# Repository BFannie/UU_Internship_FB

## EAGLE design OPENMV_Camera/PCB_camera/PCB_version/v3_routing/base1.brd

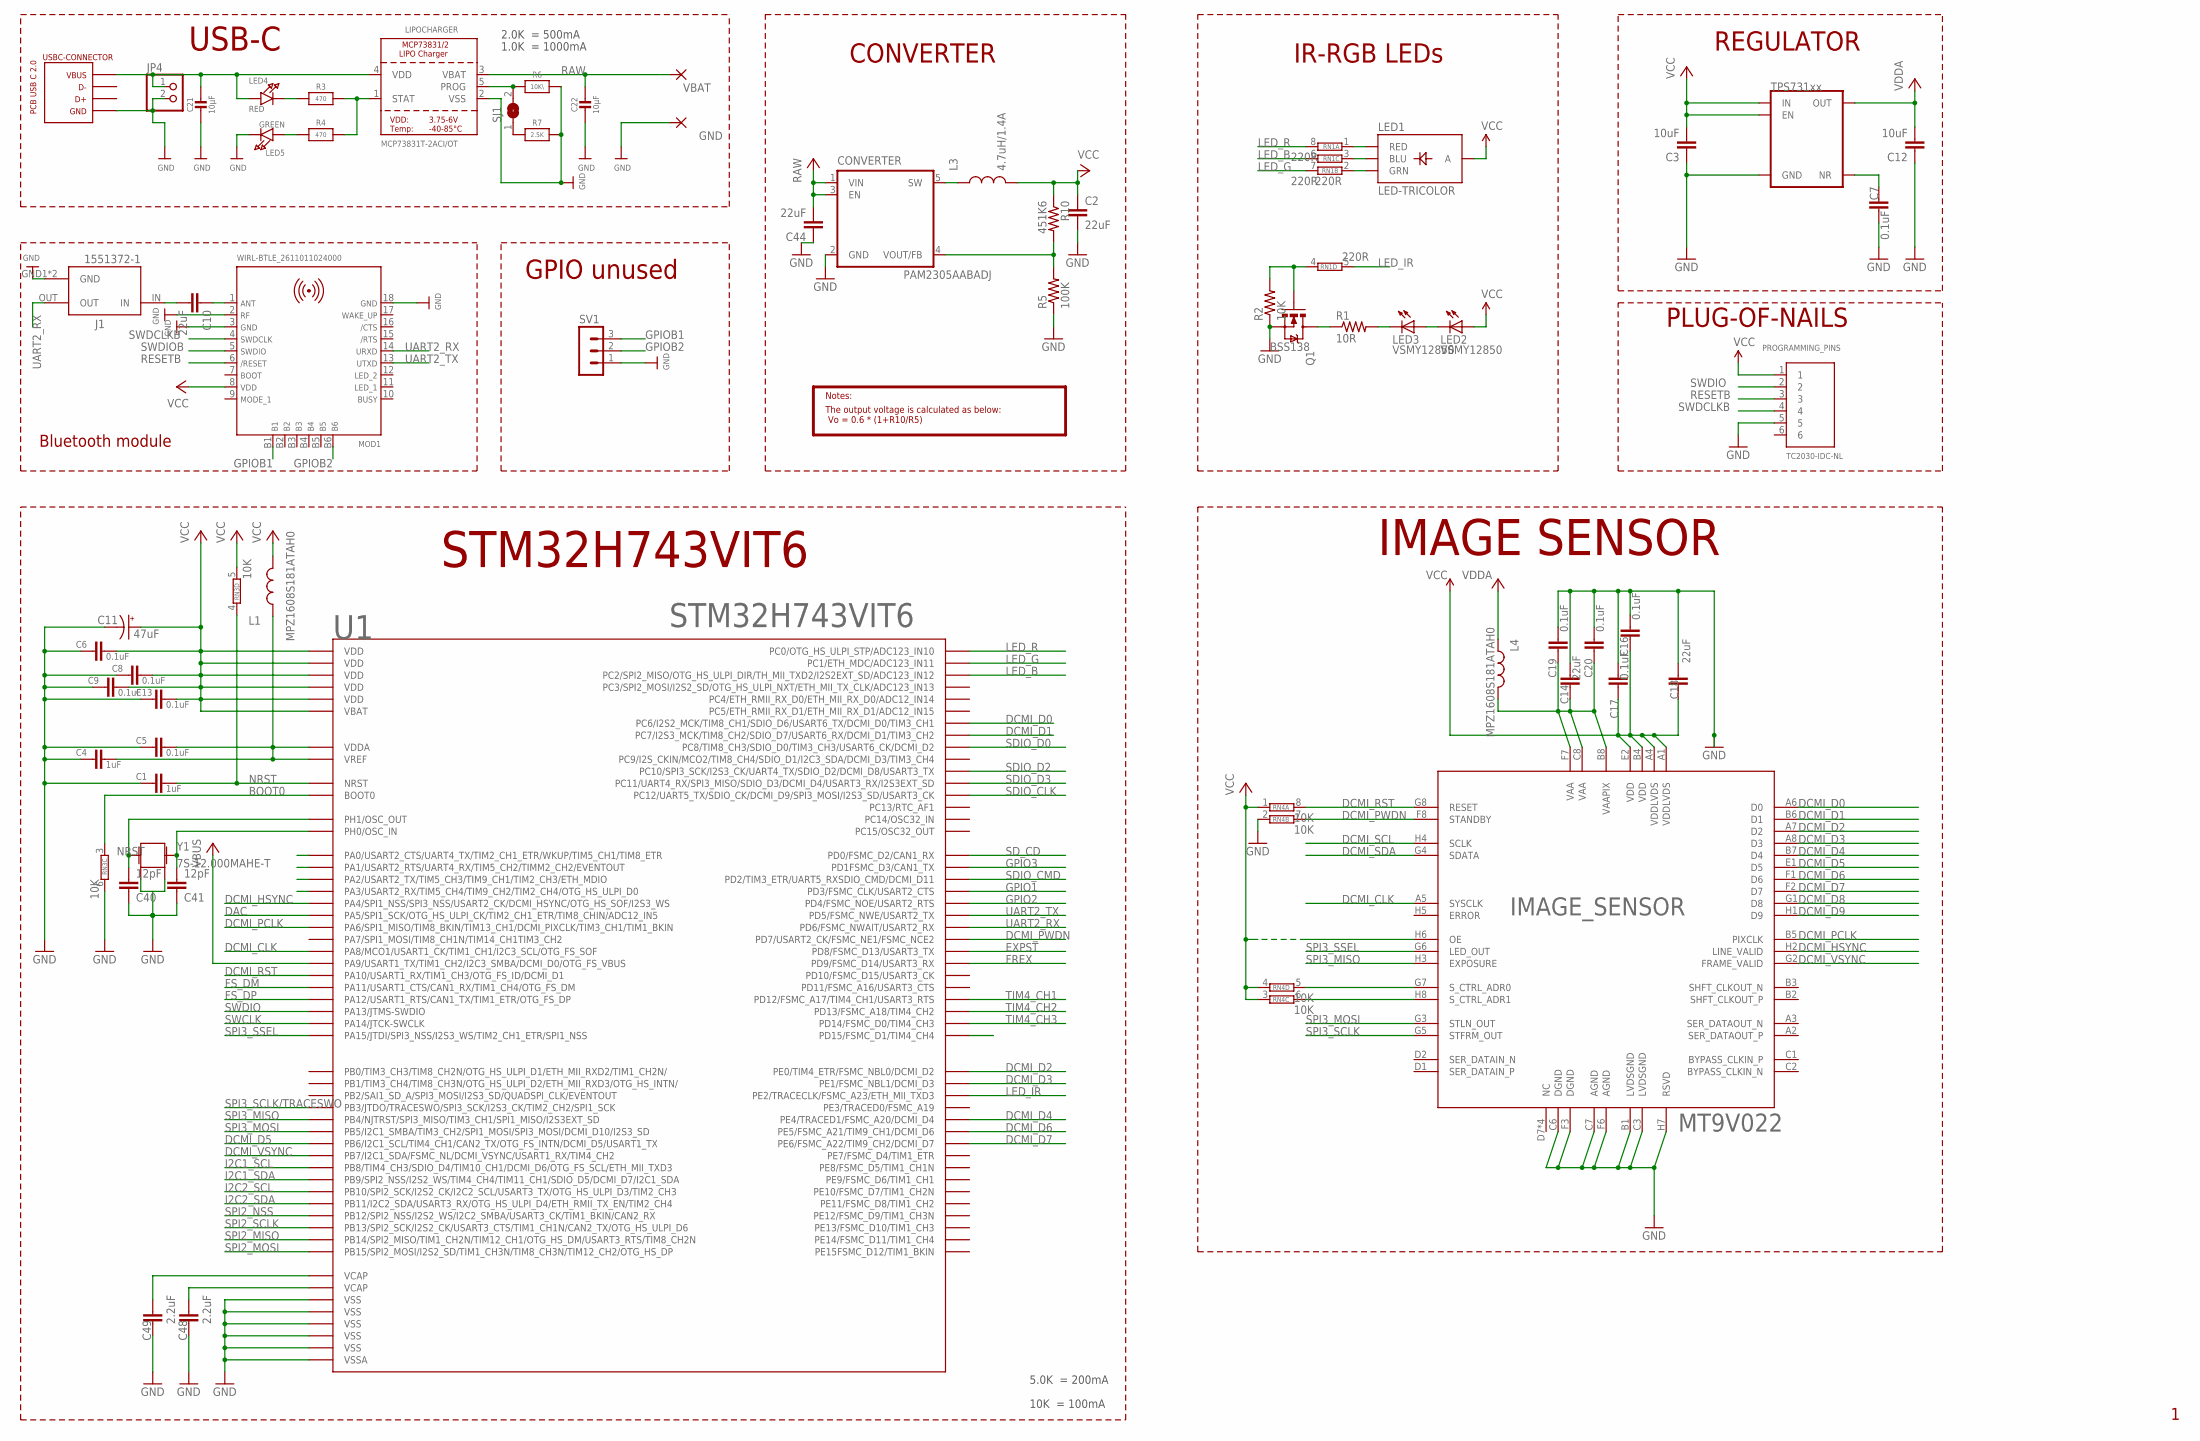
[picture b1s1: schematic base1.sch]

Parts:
C1, C4: 1uF; 0603-CAP
C2, C10, C14, C18, C44: 22uF; 0805
C3, C12: 10uF; 0805
C5, C6, C7, C8, C9, C13: 0.1uF; 0603-CAP
C11: 47uF; EIA3216
C16, C17, C19, C20: 0.1uF; 0402-CAP
C21, C22: 10µF; 0805-NO
C40, C41: 12pF; 0603-CAP
C48, C49: 2.2uF; 0603-CAP
CONVERTER: PAM2305AABADJ; TSOT25
GND: SMD2; SMD1,27-2,54
IMAGE_SENSOR: MT9V022; IBGA52
J1: 1551372-1; TE_1551372-1
JP4: HEADER-1X2ROUND; 1X02_ROUND
L1, L4: MPZ1608S181ATAH0; 0603
L3: 4.7uH/1.4A; 1007
LED1: LED-TRICOLOR; LED-TRICOLOR-SMD-MF
LED2, LED3: VSMY12850; LED-1206
LED4: RED; CHIPLED_0805_NOOUTLINE
LED5: GREEN; CHIPLED_0805_NOOUTLINE
LIPOCHARGER: MCP73831T-2ACI/OT; SOT23-5
MOD1: WIRL-BTLE_2611011024000; WE-FP-4+
PROGRAMMING_PINS: TC2030-IDC-NL; TAG_TC2030-IDC-NL
Q1: BSS138; SOT23-3
R1: 10R; 0603-RES
R2: 10K; 0603-RES
R3, R4: 470; 0805-NO
R5: 100K; 0603-RES
R6: 10K\; 0805-NO
R7: 2.5K; 0805-NO
R10: 451K6; 0603-RES
REGULATOR: TPS731XX; SOT23-5
RN1: 220R; EXBV8V
RN3, RN4: 10K; EXBV8V
SJ1: SOLDERJUMPER; SOLDERJUMPER_ARROW_NOPASTE
SV1: MA03-1
U1: STM32H743VIT6; LQFP100
USBC-CONNECTOR: PCB_USB_C_2.0DS_2; USB_TYPE_C_DS_2
VBAT: SMD2; SMD1,27-2,54
Y1: 7S-12.000MAHE-T; CRYSTAL-2.5X2.0

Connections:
BOOT0: RN3.3 (1), U1.94 (BOOT0)
DAC: U1.29 (PA5/SPI1_SCK/OTG_HS_ULPI_CK/TIM2_CH1_ET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)
DCMI_CLK: IMAGE_SENSOR.A5 (SYSCLK), U1.67 (PA8/MCO1/USART1_CK/TIM1_CH1/I2C3_SCL/OT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)
DCMI_D0: IMAGE_SENSOR.A6 (D0), U1.63 (PC6/I2S2_MCK/TIM8_CH1/SDIO_D6/USART6_TX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)
DCMI_D1: IMAGE_SENSOR.B6 (D1), U1.64 (PC7/I2S3_MCK/TIM8_CH2/SDIO_D7/USART6_RX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)
DCMI_D2: IMAGE_SENSOR.A7 (D2), U1.97 (PE0/TIM4_ETR/FSMC_NBL0/DCMI_D2)
DCMI_D3: IMAGE_SENSOR.A8 (D3), U1.98 (PE1/FSMC_NBL1/DCMI_D3)
DCMI_D4: IMAGE_SENSOR.B7 (D4), U1.3 (PE4/TRACED1/FSMC_A20/DCMI_D4)
DCMI_D5: IMAGE_SENSOR.E1 (D5), U1.92 (PB6/I2C1_SCL/TIM4_CH1/CAN2_TX/OTG_FS_IN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)
DCMI_D6: IMAGE_SENSOR.F1 (D6), U1.4 (PE5/FSMC_A21/TIM9_CH1/DCMI_D6)
DCMI_D7: IMAGE_SENSOR.F2 (D7), U1.5 (PE6/FSMC_A22/TIM9_CH2/DCMI_D7)
DCMI_D8: IMAGE_SENSOR.G1 (D8)
DCMI_D9: IMAGE_SENSOR.H1 (D9)
DCMI_HSYNC: IMAGE_SENSOR.H2 (LINE_VALID), U1.28 (PA4/SPI1_NSS/SPI3_NSS/USART2_CK/DCMI_HS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)
DCMI_PCLK: IMAGE_SENSOR.B5 (PIXCLK), U1.30 (PA6/SPI1_MISO/TIM8_BKIN/TIM13_CH1/DCMI_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)
DCMI_PWDN: IMAGE_SENSOR.F8 (STANDBY), RN4.7 (2), U1.88 (PD7/USART2_CK/FSMC_NE1/FSMC_NCE2)
DCMI_RST: IMAGE_SENSOR.G8 (RESET), RN4.8 (2), U1.69 (PA10/USART1_RX/TIM1_CH3/OTG_FS_ID/DCMI_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)
DCMI_SCL: IMAGE_SENSOR.H4 (SCLK)
DCMI_SDA: IMAGE_SENSOR.G4 (SDATA)
DCMI_VSYNC: IMAGE_SENSOR.G2 (FRAME_VALID), U1.93 (PB7/I2C1_SDA/FSMC_NL/DCMI_VSYNC/USART1_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)
EXPST: U1.55 (PD8/FSMC_D13/USART3_TX)
FREX: U1.56 (PD9/FSMC_D14/USART3_RX)
FS_DM: U1.70 (PA11/USART1_CTS/CAN1_RX/TIM1_CH4/OTG_FS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)
FS_DP: U1.71 (PA12/USART1_RTS/CAN1_TX/TIM1_ETR/OTG_FS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)
GND: C1.2, C2.2, C3.1, C4.2, C5.2, C6.2, C7.2, C8.2, C9.2, C11.C (-), C12.1, C13.2, C14.1, C16.2, C17.2, C18.1, C19.2, C20.2, C21.2, C22.2, C40.1, C41.1, C44.1, C48.2, C49.2, CONVERTER.2 (GND), GND.1, IMAGE_SENSOR.B1 (LVDSGND), IMAGE_SENSOR.C3 (LVDSGND), IMAGE_SENSOR.C6 (DGND), IMAGE_SENSOR.C7 (AGND), IMAGE_SENSOR.F3 (DGND), IMAGE_SENSOR.F6 (AGND), IMAGE_SENSOR.H7 (RSVD), J1.GND1 (GND), J1.GND2 (GND), JP4.2, LED5.C, LIPOCHARGER.2 (VSS), MOD1.2, MOD1.3, MOD1.18, PROGRAMMING_PINS.5, Q1.2 (S), R2.1, R5.1, R6.2, R7.2, REGULATOR.2 (GND), RN3.6 (2), RN4.2 (1), SV1.1, U1.10 (VSS), U1.19 (VSSA), U1.26 (VSS), U1.49 (VSS), U1.74 (VSS), U1.99 (VSS), USBC-CONNECTOR.A4 (VBUS), USBC-CONNECTOR.A9 (VBUS), USBC-CONNECTOR.B4 (VBUS), USBC-CONNECTOR.B9 (VBUS)
GPIO1: U1.84 (PD3/FSMC_CLK/USART2_CTS)
GPIO2: U1.85 (PD4/FSMC_NOE/USART2_RTS)
GPIO3: U1.82 (PD1FSMC_D3/CAN1_TX)
GPIOB1: MOD1.B1, SV1.3
GPIOB2: MOD1.B6, SV1.2
I2C1_SCL: U1.95 (PB8/TIM4_CH3/SDIO_D4/TIM10_CH1/DCMI_D6/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)
I2C1_SDA: U1.96 (PB9/SPI2_NSS/I2S2_WS/TIM4_CH4/TIM11_CH1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)
I2C2_SCL: U1.46 (PB10/SPI2_SCK/I2S2_CK/I2C2_SCL/USART3_T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)
I2C2_SDA: U1.47 (PB11/I2C2_SDA/USART3_RX/OTG_HS_ULPI_D4/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)
LED_B: RN1.6 (2), U1.17 (PC2/SPI2_MISO/OTG_HS_ULPI_DIR/TH_MII_TX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)
LED_G: RN1.7 (2), U1.16 (PC1/ETH_MDC/ADC123_IN11)
LED_IR: RN1.5 (2), U1.1 (PE2/TRACECLK/FSMC_A23/ETH_MII_TXD3)
LED_R: RN1.8 (2), U1.15 (PC0/OTG_HS_ULPI_STP/ADC123_IN10)
unnamed: LED4.C, R3.1
unnamed: C40.2, U1.13 (PH1/OSC_OUT), Y1.3 (2)
unnamed: LIPOCHARGER.1 (STAT), R3.2, R4.2
unnamed: C41.2, U1.12 (PH0/OSC_IN), Y1.1
unnamed: Q1.1 (G), R2.2, RN1.4 (1)
unnamed: LED1.B (BLU), RN1.3 (1)
unnamed: C10.2, J1.IN
unnamed: LED1.R (RED), RN1.1
unnamed: LED1.G (GRN), RN1.2 (1)
unnamed: LED3.C, R1.2
unnamed: C7.1, REGULATOR.4 (NR)
unnamed: C4.1, C5.1, L1.1, U1.20 (VREF), U1.21 (VDDA)
unnamed: CONVERTER.4 (VOUT/FB), R5.2, R10.2
unnamed: Q1.3 (D), R1.1
unnamed: LIPOCHARGER.5 (PROG), R6.1, SJ1.2
unnamed: LED5.A, R4.1
unnamed: LED2.C, LED3.A
unnamed: R7.1, SJ1.1
unnamed: IMAGE_SENSOR.G7 (S_CTRL_ADR0), RN4.5 (2)
unnamed: IMAGE_SENSOR.H8 (S_CTRL_ADR1), RN4.6 (2)
unnamed: C10.1, MOD1.1
NRST: C1.1, RN3.4 (1), U1.14 (NRST)
P$1: Y1.2, Y1.4
RAW: C22.1, C44.2, CONVERTER.1 (VIN), CONVERTER.3 (EN), LIPOCHARGER.3 (VBAT), VBAT.1
RESETB: MOD1.6, PROGRAMMING_PINS.3
SDIO_CLK: U1.80 (PC12/UART5_TX/SDIO_CK/DCMI_D9/SPI3_MOSI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)
SDIO_CMD: U1.83 (PD2/TIM3_ETR/UART5_RXSDIO_CMD/DCMI_D11)
SDIO_D0: U1.65 (PC8/TIM8_CH3/SDIO_D0/TIM3_CH3/USART6_CK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)
SDIO_D2: U1.78 (PC10/SPI3_SCK/I2S3_CK/UART4_TX/SDIO_D2/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)
SDIO_D3: U1.79 (PC11/UART4_RX/SPI3_MISO/SDIO_D3/DCMI_D4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)
SD_CD: U1.81 (PD0/FSMC_D2/CAN1_RX)
SPI2_MISO: U1.53 (PB14/SPI2_MISO/TIM1_CH2N/TIM12_CH1/OTG_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)
SPI2_MOSI: U1.54 (PB15/SPI2_MOSI/I2S2_SD/TIM1_CH3N/TIM8_C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)
SPI2_NSS: U1.51 (PB12/SPI2_NSS/I2S2_WS/I2C2_SMBA/USART3_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)
SPI2_SCLK: U1.52 (PB13/SPI2_SCK/I2S2_CK/USART3_CTS/TIM1_C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)
SPI3_MISO: IMAGE_SENSOR.H3 (EXPOSURE), U1.90 (PB4/NJTRST/SPI3_MISO/TIM3_CH1/SPI1_MISO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)
SPI3_MOSI: IMAGE_SENSOR.G3 (STLN_OUT), U1.91 (PB5/I2C1_SMBA/TIM3_CH2/SPI1_MOSI/SPI3_M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)
SPI3_SCLK: IMAGE_SENSOR.G5 (STFRM_OUT)
SPI3_SCLK/TRACESWO: U1.89 (PB3/JTDO/TRACESWO/SPI3_SCK/I2S3_CK/TIM2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)
SPI3_SSEL: IMAGE_SENSOR.G6 (LED_OUT), U1.77 (PA15/JTDI/SPI3_NSS/I2S3_WS/TIM2_CH1_ETR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)
SW: CONVERTER.5 (SW), L3.1
SWCLK: U1.76 (PA14/JTCK-SWCLK)
SWDCLKB: MOD1.4, PROGRAMMING_PINS.4
SWDIO: PROGRAMMING_PINS.2, U1.72 (PA13/JTMS-SWDIO)
SWDIOB: MOD1.5
TIM4_CH1: U1.59 (PD12/FSMC_A17/TIM4_CH1/USART3_RTS)
TIM4_CH2: U1.60 (PD13/FSMC_A18/TIM4_CH2)
TIM4_CH3: U1.61 (PD14/FSMC_D0/TIM4_CH3)
UART2_RX: J1.OUT, MOD1.14, U1.87 (PD6/FSMC_NWAIT/USART2_RX)
UART2_TX: MOD1.13, U1.86 (PD5/FSMC_NWE/USART2_TX)
VAA: C14.2, C19.1, C20.1, IMAGE_SENSOR.B8 (VAAPIX), IMAGE_SENSOR.C8 (VAA), IMAGE_SENSOR.F7 (VAA), L4.2
VBAT: C2.1, C3.2, C6.1, C8.1, C9.1, C11.A (+), C13.1, C16.1, C17.1, C18.2, IMAGE_SENSOR.A1 (VDDLVDS), IMAGE_SENSOR.A4 (VDDLVDS), IMAGE_SENSOR.B4 (VDD), IMAGE_SENSOR.E2 (VDD), IMAGE_SENSOR.H6 (OE), L1.2, L3.2, LED1.A, LED2.A, R10.1, REGULATOR.1 (IN), REGULATOR.3 (EN), RN3.5 (2), RN4.1, RN4.3 (1), RN4.4 (1), U1.6 (VBAT), U1.11 (VDD), U1.27 (VDD), U1.50 (VDD), U1.75 (VDD), U1.100 (VDD)
VBUS: U1.68 (PA9/USART1_TX/TIM1_CH2/I2C3_SMBA/DCMI_D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)
VCAP1: C49.1, U1.48 (VCAP)
VCAP2: C48.1, U1.73 (VCAP)
VCC: MOD1.8, PROGRAMMING_PINS.1
VDD: C21.1, JP4.1, LED4.A, LIPOCHARGER.4 (VDD), USBC-CONNECTOR.A1 (GND), USBC-CONNECTOR.A12 (GND), USBC-CONNECTOR.B1 (GND), USBC-CONNECTOR.B12 (GND)
VDDA: C12.2, L4.1, REGULATOR.5 (OUT)

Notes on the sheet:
STM32H743VIT6
IR-RGB LEDs
USB-C
The output voltage is calculated as below: Vo = 0.6 * (1+R10/R5)
Notes:
10K = 100mA
5.0K = 200mA
2.0K = 500mA
1.0K = 1000mA
CONVERTER
REGULATOR
GPIO unused
Bluetooth module
IMAGE SENSOR
PLUG-OF-NAILS

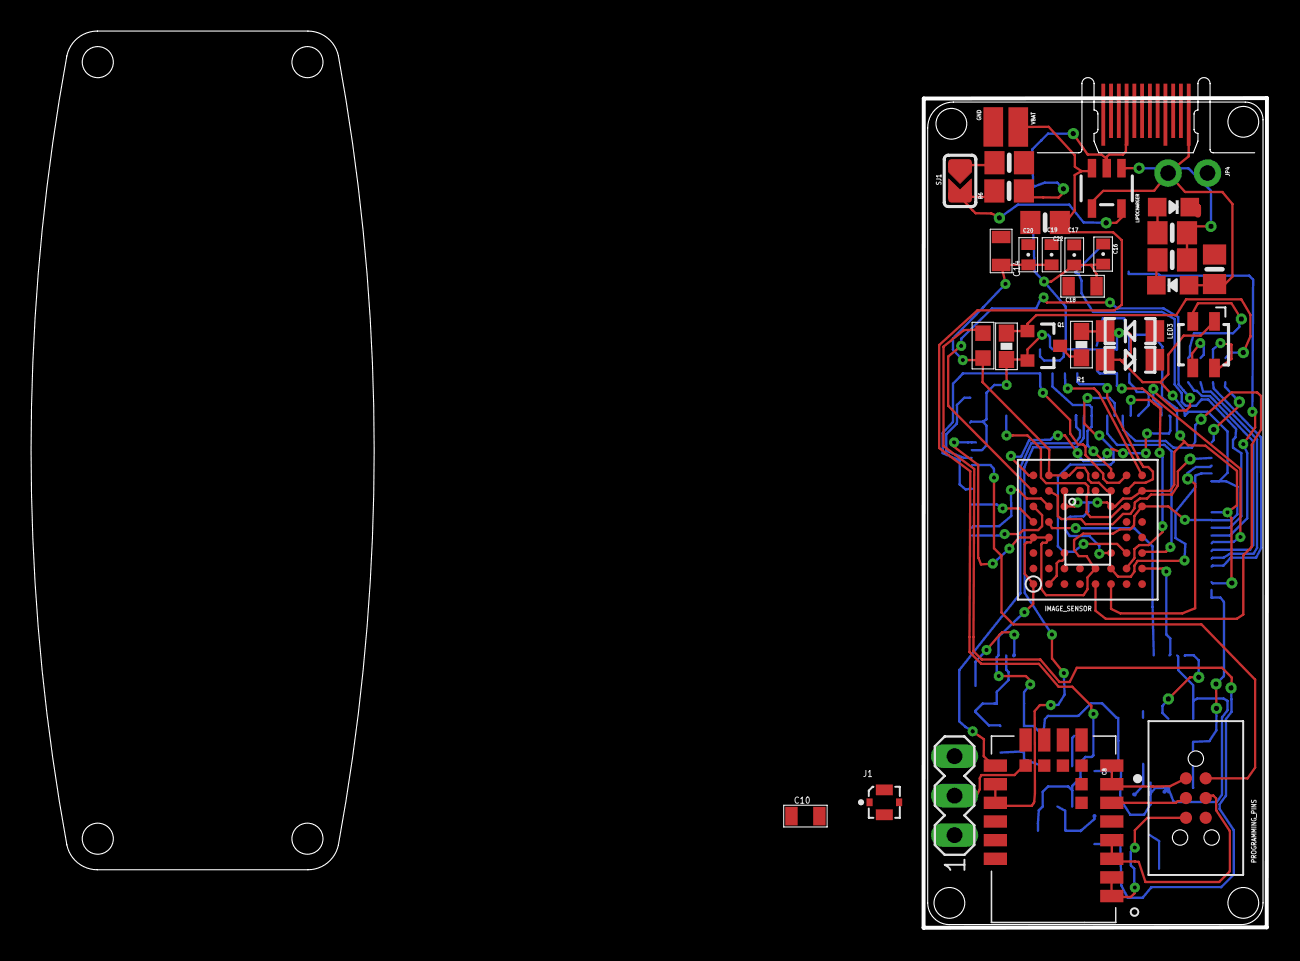
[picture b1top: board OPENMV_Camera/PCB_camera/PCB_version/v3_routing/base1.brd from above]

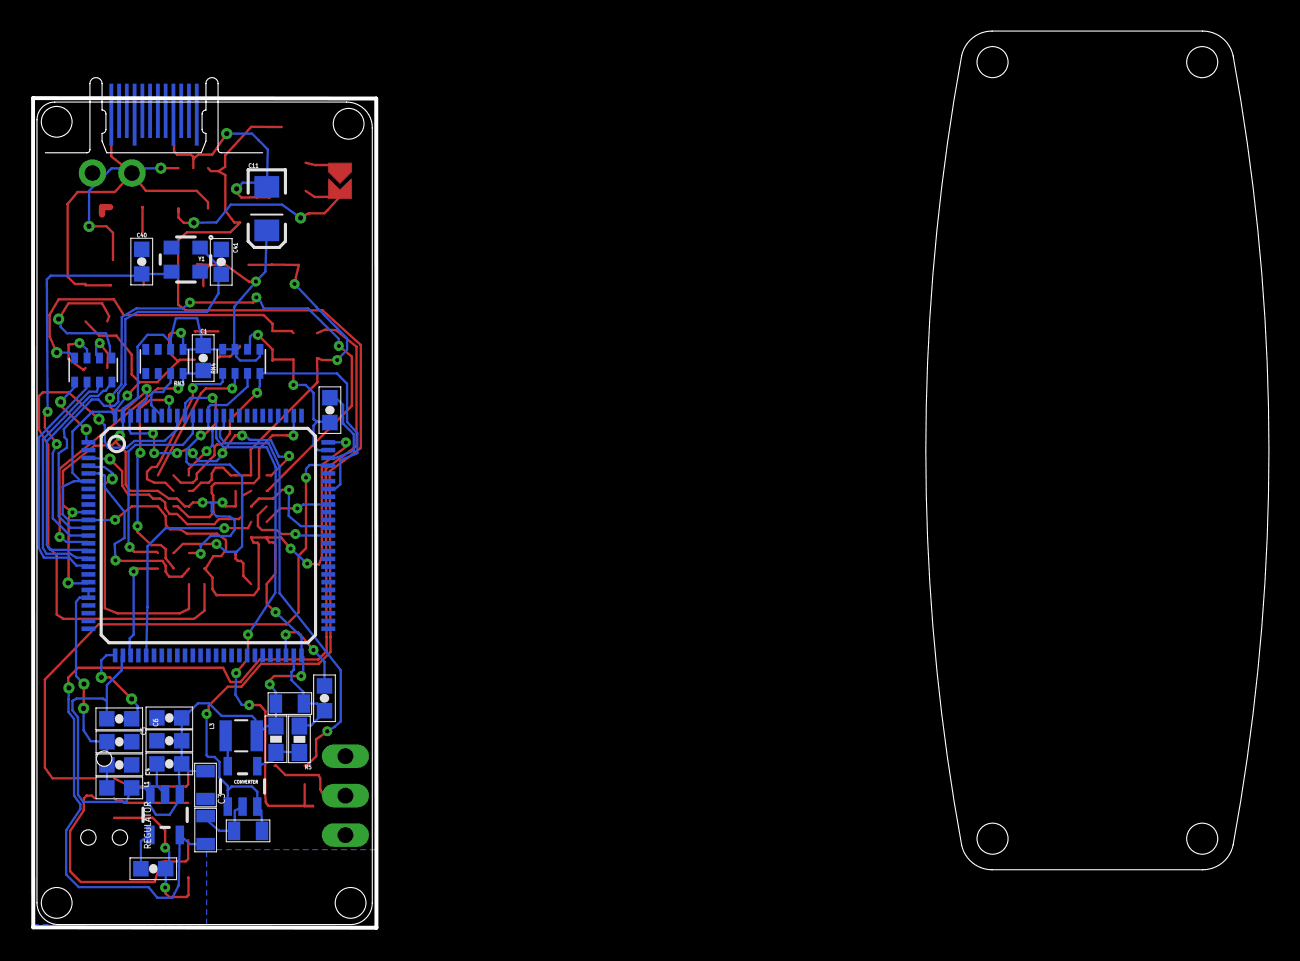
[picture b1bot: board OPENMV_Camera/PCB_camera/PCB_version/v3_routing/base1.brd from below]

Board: 2 copper layers, 22.1 x 53.4 mm, 61 parts (29 on the bottom side), 62 nets.

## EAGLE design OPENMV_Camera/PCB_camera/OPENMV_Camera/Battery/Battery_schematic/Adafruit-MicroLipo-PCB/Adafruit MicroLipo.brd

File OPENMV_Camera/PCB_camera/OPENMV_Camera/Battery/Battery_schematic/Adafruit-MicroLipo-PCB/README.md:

# Adafruit MicroLipo and MiniLipo Charging Boards/Backpacks

&nbsp; 
<br />
&nbsp; 
<br />
&nbsp; 
<br />

Click to purchase from the Adafruit Shop:
- [Adafruit Micro-Lipo Charger for LiPo/LiIon Batt w/MicroUSB Jack - v1](https://www.adafruit.com/product/1904)
- [Adafruit Micro Lipo - USB LiIon/LiPoly charger - v1](https://www.adafruit.com/product/1304)
- [Adafruit Mini Lipo w/Mini-B USB Jack - USB LiIon/LiPoly charger - v1](https://www.adafruit.com/product/1905)
- [Adafruit LiIon/LiPoly Backpack Add-On for Pro Trinket/ItsyBitsy](https://www.adafruit.com/product/2124)
- [Adafruit Micro-Lipo Charger for LiPoly Batt with USB Type C Jack](https://www.adafruit.com/product/4410)
- [Adafruit Micro Lipo - USB LiIon/LiPoly charger - v2](https://www.adafruit.com/product/1304)

Oh so handy, this little lipo charger is so small and easy to use you can keep it on your desk or mount it easily into any project! Simply plug it via any MicroUSB cable into a USB port and a 3.7V/4.2V lithium polymer or lithium ion rechargeable battery into the JST plug on the other end. There are two LEDs - one red and one green. While charging, the red LED is lit. When the battery is fully charged and ready for use, the green LED turns on. Seriously, it could not get more easy.

These are the PCB files for the Adafruit Mini/MicroLipo battery chargers. The 
Format is EagleCAD schematic and board layout.

### License

Adafruit invests time and resources providing this open source design, please support Adafruit and open-source hardware by purchasing products from [Adafruit](https://www.adafruit.com)!

All text above must be included in any redistribution

Designed by Limor Fried/Ladyada for Adafruit Industries.
Creative Commons Attribution/Share-Alike, all text above must be included in any redistribution. 
See license.txt for additional information.

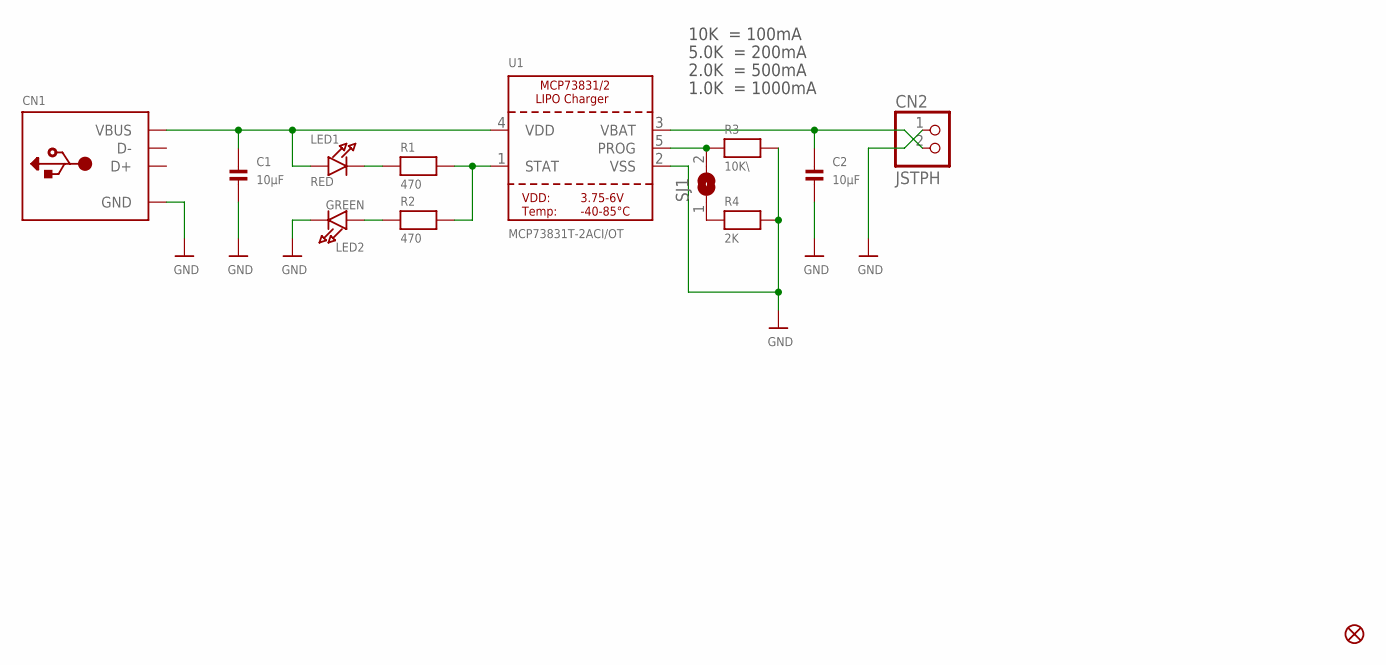
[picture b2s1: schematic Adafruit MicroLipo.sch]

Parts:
C1, C2: 10µF; 0805
CN1: USB_TYPEAPCB; USBA_PCB
CN2: JSTPH; JSTPH2
FID1: FIDUCIAL""; FIDUCIAL_1MM
LED1: RED; CHIPLED_0805
LED2: GREEN; CHIPLED_0805
R1, R2: 470; 0805
R3: 10K\; 0805
R4: 2K; 0805
SJ1: SOLDERJUMPER; SOLDERJUMPER_ARROW_NOPASTE
U1: MCP73831T-2ACI/OT; SOT23-5

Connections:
GND: C1.2, C2.2, CN1.GND, CN2.1, LED2.C, R3.2, R4.2, U1.2 (VSS)
unnamed: LED1.C, R1.1
unnamed: R1.2, R2.2, U1.1 (STAT)
unnamed: R4.1, SJ1.1
unnamed: R3.1, SJ1.2, U1.5 (PROG)
unnamed: LED2.A, R2.1
VBAT: C2.1, CN2.2, U1.3 (VBAT)
VDD: C1.1, CN1.VCC (VBUS), LED1.A, U1.4 (VDD)

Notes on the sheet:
10K = 100mA
5.0K = 200mA
2.0K = 500mA
1.0K = 1000mA

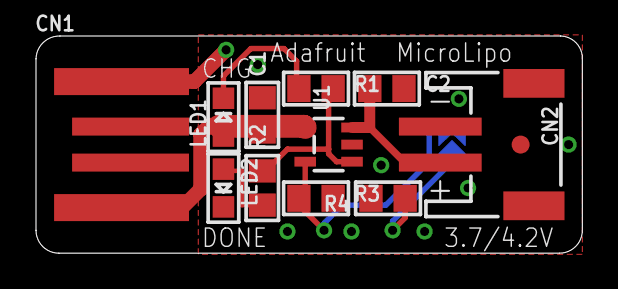
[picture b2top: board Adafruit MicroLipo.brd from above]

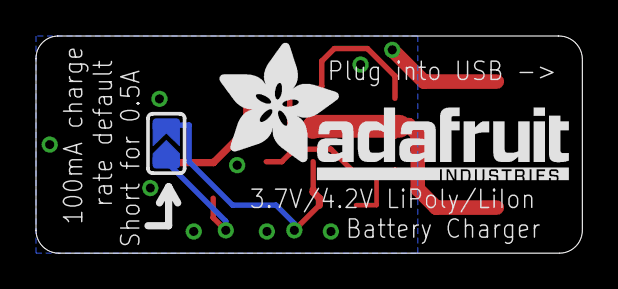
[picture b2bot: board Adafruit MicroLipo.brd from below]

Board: 2 copper layers, 30.4 x 12.1 mm, 14 parts (2 on the bottom side), 8 nets.

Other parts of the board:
U$8: ADAFRUIT_TEXT_20MM

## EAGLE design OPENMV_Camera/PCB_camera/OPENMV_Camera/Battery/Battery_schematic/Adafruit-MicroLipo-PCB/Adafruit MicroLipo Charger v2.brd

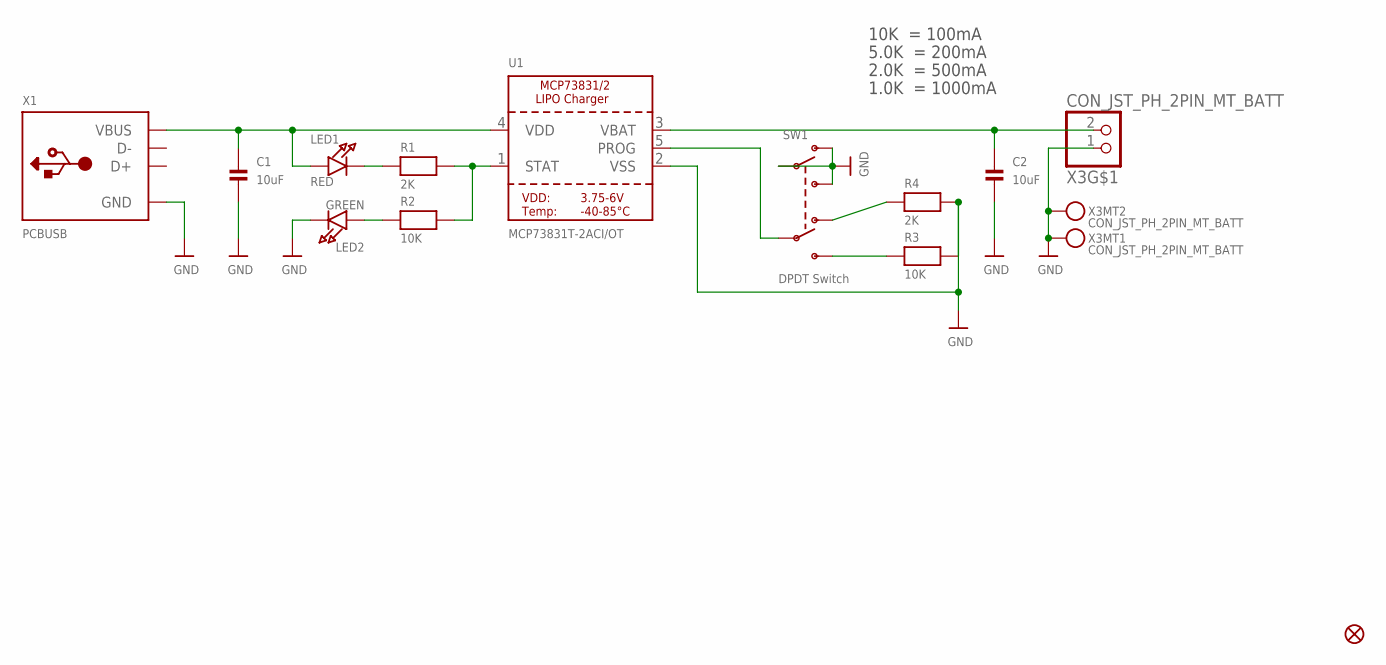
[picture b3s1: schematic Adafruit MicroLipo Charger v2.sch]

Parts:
C1, C2: 10uF; 0805-NO
FID1: FIDUCIAL_1MM
LED1: RED; CHIPLED_0603_NOOUTLINE
LED2: GREEN; CHIPLED_0603_NOOUTLINE
R1, R4: 2K; 0603-NO
R2, R3: 10K; 0603-NO
SW1: DPDT Switch; EG1390
U1: MCP73831T-2ACI/OT; SOT23-5
X1: PCBUSB; USBA_PCB
X3: CON_JST_PH_2PIN_MT_BATT; JSTPH2_BATT

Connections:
GND: C1.2, C2.2, LED2.C, R3.2, R4.2, SW1.O1, SW1.P1, SW1.S1, U1.2 (VSS), X1.GND, X3.1, X3.NC1, X3.NC2
unnamed: LED1.C, R1.1
unnamed: R1.2, R2.2, U1.1 (STAT)
unnamed: R3.1, SW1.S2
unnamed: R4.1, SW1.O2
unnamed: SW1.P2, U1.5 (PROG)
unnamed: LED2.A, R2.1
VBAT: C2.1, U1.3 (VBAT), X3.2
VDD: C1.1, LED1.A, U1.4 (VDD), X1.VCC (VBUS)

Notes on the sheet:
10K = 100mA
5.0K = 200mA
2.0K = 500mA
1.0K = 1000mA

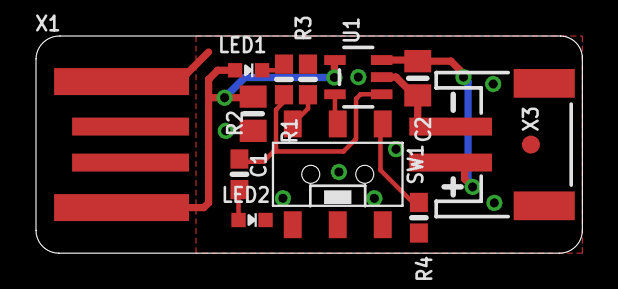
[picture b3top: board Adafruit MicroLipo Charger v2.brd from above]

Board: 2 copper layers, 30.4 x 12.1 mm, 27 parts (5 on the bottom side), 9 nets.

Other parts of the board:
PLABEL0: PLABEL0
PLABEL1: PLABEL1
PLABEL2: PLABEL2
PLABEL3: PLABEL3
PLABEL4: PLABEL4
PLABEL5: PLABEL5
PLABEL6: PLABEL6
PLABEL7: PLABEL7
PLABEL8: PLABEL8
PLABEL9: PLABEL9
PLABEL10: PLABEL10
PLABEL11: PLABEL11
U$8: ADAFRUIT_TEXT_20MM
U$9: PCBFEAT-REV-040

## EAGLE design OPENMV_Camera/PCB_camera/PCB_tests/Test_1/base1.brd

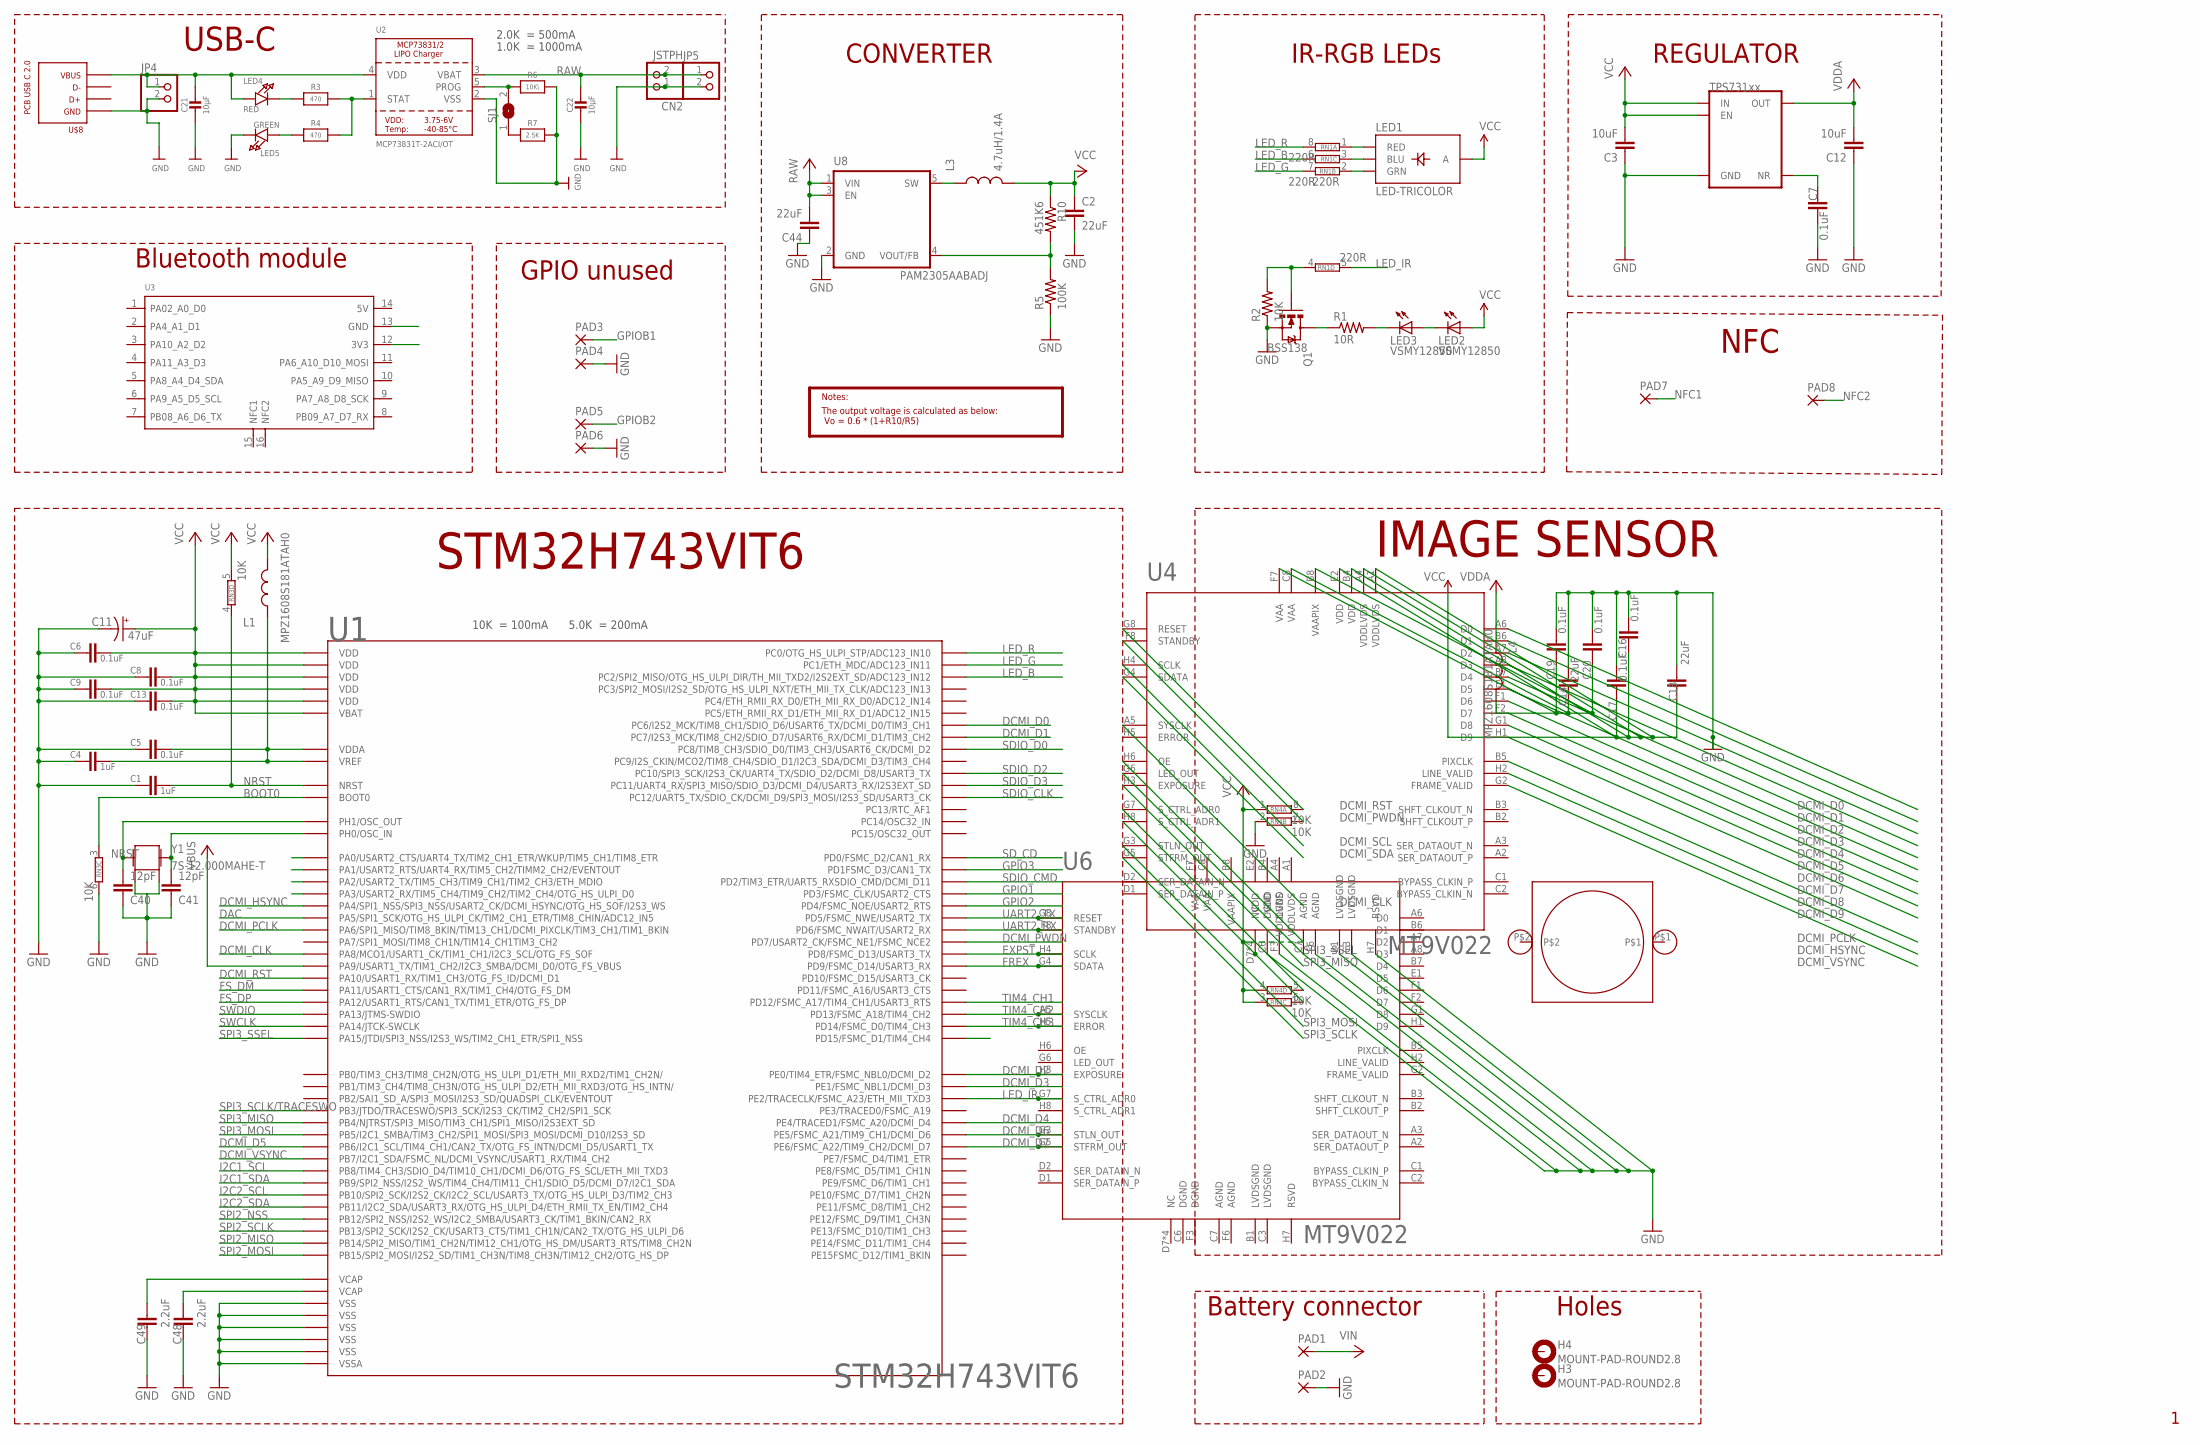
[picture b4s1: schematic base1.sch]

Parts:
C1, C4: 1uF; 0603-CAP
C2, C14, C18, C44: 22uF; 0805
C3, C12: 10uF; 0805
C5, C6, C7, C8, C9, C13: 0.1uF; 0603-CAP
C11: 47uF; EIA3216
C16, C17, C19, C20: 0.1uF; 0402-CAP
C21, C22: 10µF; 0805-NO
C40, C41: 12pF; 0603-CAP
C48, C49: 2.2uF; 0603-CAP
CN2: JSTPH; JSTPH2
H3, H4: MOUNT-PAD-ROUND2.8; 2,8-PAD
JP4, JP5: HEADER-1X2ROUND; 1X02_ROUND
L1, L4: MPZ1608S181ATAH0; 0603
L3: 4.7uH/1.4A; 1007
LED1: LED-TRICOLOR; LED-TRICOLOR-SMD-MF
LED2, LED3: VSMY12850; LED-1206
LED4: RED; CHIPLED_0805_NOOUTLINE
LED5: GREEN; CHIPLED_0805_NOOUTLINE
LM1: LENSMOUNT20MM; LENSMOUNT-20MM
PAD1, PAD2, PAD3, PAD4, PAD5, PAD6, PAD7, PAD8: SMD2; SMD1,27-2,54
Q1: BSS138; SOT23-3
R1: 10R; 0603-RES
R2: 10K; 0603-RES
R3, R4: 470; 0805-NO
R5: 100K; 0603-RES
R6: 10K\; 0805-NO
R7: 2.5K; 0805-NO
R10: 451K6; 0603-RES
RN1: 220R; EXBV8V
RN3, RN4: 10K; EXBV8V
SJ1: SOLDERJUMPER; SOLDERJUMPER_ARROW_NOPASTE
U1: STM32H743VIT6; LQFP100
U2: MCP73831T-2ACI/OT; SOT23-5
U3: MOUDLE-SEEEDUINO-XIAO-NRF52840-SENSE-SMD; MOUDLE16P-SMD-2.54-21X17.8MM
U4, U6: MT9V022; IBGA52
U5: TPS731XX; SOT23-5
U8: PAM2305AABADJ; TSOT25
U$8: PCB_USB_C_2.0DS_2; USB_TYPE_C_DS_2
Y1: 7S-12.000MAHE-T; CRYSTAL-2.5X2.0

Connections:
AGND: U6.C7 (AGND), U6.F6 (AGND)
BOOT0: RN3.3 (1), U1.94 (BOOT0)
DAC: U1.29 (PA5/SPI1_SCK/OTG_HS_ULPI_CK/TIM2_CH1_ET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)
DCMI_CLK: U1.67 (PA8/MCO1/USART1_CK/TIM1_CH1/I2C3_SCL/OT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), U4.A5 (SYSCLK)
DCMI_D0: U1.63 (PC6/I2S2_MCK/TIM8_CH1/SDIO_D6/USART6_TX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), U4.A6 (D0)
DCMI_D1: U1.64 (PC7/I2S3_MCK/TIM8_CH2/SDIO_D7/USART6_RX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), U4.B6 (D1)
DCMI_D2: U1.97 (PE0/TIM4_ETR/FSMC_NBL0/DCMI_D2), U4.A7 (D2), U6.H3 (EXPOSURE)
DCMI_D3: U1.98 (PE1/FSMC_NBL1/DCMI_D3), U4.A8 (D3)
DCMI_D4: U1.3 (PE4/TRACED1/FSMC_A20/DCMI_D4), U4.B7 (D4)
DCMI_D5: U1.92 (PB6/I2C1_SCL/TIM4_CH1/CAN2_TX/OTG_FS_IN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), U4.E1 (D5)
DCMI_D6: U1.4 (PE5/FSMC_A21/TIM9_CH1/DCMI_D6), U4.F1 (D6), U6.G3 (STLN_OUT)
DCMI_D7: U1.5 (PE6/FSMC_A22/TIM9_CH2/DCMI_D7), U4.F2 (D7), U6.G5 (STFRM_OUT)
DCMI_D8: U4.G1 (D8)
DCMI_D9: U4.H1 (D9)
DCMI_HSYNC: U1.28 (PA4/SPI1_NSS/SPI3_NSS/USART2_CK/DCMI_HS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), U4.H2 (LINE_VALID)
DCMI_PCLK: U1.30 (PA6/SPI1_MISO/TIM8_BKIN/TIM13_CH1/DCMI_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), U4.B5 (PIXCLK)
DCMI_PWDN: RN4.7 (2), U1.88 (PD7/USART2_CK/FSMC_NE1/FSMC_NCE2), U4.F8 (STANDBY)
DCMI_RST: RN4.8 (2), U1.69 (PA10/USART1_RX/TIM1_CH3/OTG_FS_ID/DCMI_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), U4.G8 (RESET)
DCMI_SCL: U4.H4 (SCLK)
DCMI_SDA: U4.G4 (SDATA)
DCMI_VSYNC: U1.93 (PB7/I2C1_SDA/FSMC_NL/DCMI_VSYNC/USART1_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), U4.G2 (FRAME_VALID)
DGND: U6.C6 (DGND), U6.F3 (DGND)
EXPST: U1.55 (PD8/FSMC_D13/USART3_TX), U6.H4 (SCLK)
FREX: U1.56 (PD9/FSMC_D14/USART3_RX), U6.G4 (SDATA)
FS_DM: U1.70 (PA11/USART1_CTS/CAN1_RX/TIM1_CH4/OTG_FS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)
FS_DP: U1.71 (PA12/USART1_RTS/CAN1_TX/TIM1_ETR/OTG_FS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)
GND: C1.2, C2.2, C3.1, C4.2, C5.2, C6.2, C7.2, C8.2, C9.2, C11.C (-), C12.1, C13.2, C14.1, C16.2, C17.2, C18.1, C19.2, C20.2, C21.2, C22.2, C40.1, C41.1, C44.1, C48.2, C49.2, CN2.1, JP4.2, JP5.2, LED5.C, PAD2.1, PAD4.1, PAD6.1, Q1.2 (S), R2.1, R5.1, R6.2, R7.2, RN3.6 (2), RN4.2 (1), U1.10 (VSS), U1.19 (VSSA), U1.26 (VSS), U1.49 (VSS), U1.74 (VSS), U1.99 (VSS), U2.2 (VSS), U4.B1 (LVDSGND), U4.C3 (LVDSGND), U4.C6 (DGND), U4.C7 (AGND), U4.F3 (DGND), U4.F6 (AGND), U4.H7 (RSVD), U5.2 (GND), U8.2 (GND), U$8.A4 (VBUS), U$8.A9 (VBUS), U$8.B4 (VBUS), U$8.B9 (VBUS), Y1.2, Y1.4
GPIO1: U1.84 (PD3/FSMC_CLK/USART2_CTS)
GPIO2: U1.85 (PD4/FSMC_NOE/USART2_RTS)
GPIO3: U1.82 (PD1FSMC_D3/CAN1_TX)
GPIOB1: PAD3.1
GPIOB2: PAD5.1
I2C1_SCL: U1.95 (PB8/TIM4_CH3/SDIO_D4/TIM10_CH1/DCMI_D6/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)
I2C1_SDA: U1.96 (PB9/SPI2_NSS/I2S2_WS/TIM4_CH4/TIM11_CH1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)
I2C2_SCL: U1.46 (PB10/SPI2_SCK/I2S2_CK/I2C2_SCL/USART3_T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)
I2C2_SDA: U1.47 (PB11/I2C2_SDA/USART3_RX/OTG_HS_ULPI_D4/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)
LED_B: RN1.6 (2), U1.17 (PC2/SPI2_MISO/OTG_HS_ULPI_DIR/TH_MII_TX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)
LED_G: RN1.7 (2), U1.16 (PC1/ETH_MDC/ADC123_IN11)
LED_IR: RN1.5 (2), U1.1 (PE2/TRACECLK/FSMC_A23/ETH_MII_TXD3), U6.G7 (S_CTRL_ADR0)
LED_R: RN1.8 (2), U1.15 (PC0/OTG_HS_ULPI_STP/ADC123_IN10)
LVDSGND: U6.B1 (LVDSGND), U6.C3 (LVDSGND)
unnamed: LED4.C, R3.1
unnamed: C40.2, U1.13 (PH1/OSC_OUT), Y1.3 (2)
unnamed: R3.2, R4.2, U2.1 (STAT)
unnamed: C41.2, U1.12 (PH0/OSC_IN), Y1.1
unnamed: Q1.1 (G), R2.2, RN1.4 (1)
unnamed: LED1.B (BLU), RN1.3 (1)
unnamed: LED1.R (RED), RN1.1
unnamed: LED1.G (GRN), RN1.2 (1)
unnamed: LED3.C, R1.2
unnamed: C7.1, U5.4 (NR)
unnamed: C4.1, C5.1, L1.1, U1.20 (VREF), U1.21 (VDDA)
unnamed: R5.2, R10.2, U8.4 (VOUT/FB)
unnamed: Q1.3 (D), R1.1
unnamed: R6.1, SJ1.2, U2.5 (PROG)
unnamed: LED5.A, R4.1
unnamed: LED2.C, LED3.A
unnamed: R7.1, SJ1.1
unnamed: RN4.5 (2), U4.G7 (S_CTRL_ADR0)
unnamed: RN4.6 (2), U4.D7 (NC), U4.D8 (NC), U4.E7 (NC), U4.E8 (NC), U4.H8 (S_CTRL_ADR1)
NRST: C1.1, RN3.4 (1), U1.14 (NRST)
RAW: C22.1, C44.2, CN2.2, JP5.1, U2.3 (VBAT), U8.1 (VIN), U8.3 (EN)
RSVD: U6.H7 (RSVD)
SDIO_CLK: U1.80 (PC12/UART5_TX/SDIO_CK/DCMI_D9/SPI3_MOSI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)
SDIO_CMD: U1.83 (PD2/TIM3_ETR/UART5_RXSDIO_CMD/DCMI_D11)
SDIO_D0: U1.65 (PC8/TIM8_CH3/SDIO_D0/TIM3_CH3/USART6_CK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)
SDIO_D2: U1.78 (PC10/SPI3_SCK/I2S3_CK/UART4_TX/SDIO_D2/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)
SDIO_D3: U1.79 (PC11/UART4_RX/SPI3_MISO/SDIO_D3/DCMI_D4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)
SD_CD: U1.81 (PD0/FSMC_D2/CAN1_RX)
SPI2_MISO: U1.53 (PB14/SPI2_MISO/TIM1_CH2N/TIM12_CH1/OTG_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)
SPI2_MOSI: U1.54 (PB15/SPI2_MOSI/I2S2_SD/TIM1_CH3N/TIM8_C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)
SPI2_NSS: U1.51 (PB12/SPI2_NSS/I2S2_WS/I2C2_SMBA/USART3_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)
SPI2_SCLK: U1.52 (PB13/SPI2_SCK/I2S2_CK/USART3_CTS/TIM1_C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)
SPI3_MISO: U1.90 (PB4/NJTRST/SPI3_MISO/TIM3_CH1/SPI1_MISO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), U4.H3 (EXPOSURE)
SPI3_MOSI: U1.91 (PB5/I2C1_SMBA/TIM3_CH2/SPI1_MOSI/SPI3_M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), U4.G3 (STLN_OUT)
SPI3_SCLK: U4.G5 (STFRM_OUT)
SPI3_SCLK/TRACESWO: U1.89 (PB3/JTDO/TRACESWO/SPI3_SCK/I2S3_CK/TIM2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)
SPI3_SSEL: U1.77 (PA15/JTDI/SPI3_NSS/I2S3_WS/TIM2_CH1_ETR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), U4.G6 (LED_OUT)
SW: L3.1, U8.5 (SW)
SWCLK: U1.76 (PA14/JTCK-SWCLK)
SWDIO: U1.72 (PA13/JTMS-SWDIO)
TIM4_CH1: U1.59 (PD12/FSMC_A17/TIM4_CH1/USART3_RTS)
TIM4_CH2: U1.60 (PD13/FSMC_A18/TIM4_CH2), U6.A5 (SYSCLK)
TIM4_CH3: U1.61 (PD14/FSMC_D0/TIM4_CH3), U6.H5 (ERROR)
UART2_RX: U1.87 (PD6/FSMC_NWAIT/USART2_RX), U6.F8 (STANDBY)
UART2_TX: U1.86 (PD5/FSMC_NWE/USART2_TX), U6.G8 (RESET)
VAA: C14.2, C19.1, C20.1, L4.2, U4.B8 (VAAPIX), U4.C8 (VAA), U4.F7 (VAA), U6.C8 (VAA), U6.F7 (VAA)
VAAPIX: U6.B8 (VAAPIX)
VBAT: C2.1, C3.2, C6.1, C8.1, C9.1, C11.A (+), C13.1, C16.1, C17.1, C18.2, L1.2, L3.2, LED1.A, LED2.A, R10.1, RN3.5 (2), RN4.1, RN4.3 (1), RN4.4 (1), U1.6 (VBAT), U1.11 (VDD), U1.27 (VDD), U1.50 (VDD), U1.75 (VDD), U1.100 (VDD), U4.A1 (VDDLVDS), U4.A4 (VDDLVDS), U4.B4 (VDD), U4.E2 (VDD), U4.H6 (OE), U5.1 (IN), U5.3 (EN)
VBUS: U1.68 (PA9/USART1_TX/TIM1_CH2/I2C3_SMBA/DCMI_D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)
VCAP1: C49.1, U1.48 (VCAP)
VCAP2: C48.1, U1.73 (VCAP)
VDD: C21.1, JP4.1, LED4.A, U2.4 (VDD), U6.B4 (VDD), U6.E2 (VDD), U$8.A1 (GND), U$8.A12 (GND), U$8.B1 (GND), U$8.B12 (GND)
VDDA: C12.2, L4.1, U5.5 (OUT)
VIN: PAD1.1

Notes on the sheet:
STM32H743VIT6
IR-RGB LEDs
USB-C
Battery connector
The output voltage is calculated as below: Vo = 0.6 * (1+R10/R5)
Notes:
10K = 100mA
5.0K = 200mA
2.0K = 500mA
1.0K = 1000mA
CONVERTER
REGULATOR
GPIO unused
Bluetooth module
IMAGE SENSOR
Holes
NFC

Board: 2 copper layers, 69 parts (0 on the bottom side), 60 nets, no tracks yet.

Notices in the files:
OPENMV_Camera/PCB_camera/PCB_tests/PCB_modified/base.sch:
Copyright (c) 2018 OpenMV
This work is licensed under the Creative Commons Attribution-ShareAlike 3.0 License.
To view a copy of this license, visit http://creativecommons.org/licenses/by-sa/3.0
parts and their libraries:
01_SparkFun: Licensing: CC v3.0 Share-Alike You are welcome to use this library for commercial purposes.
microbuilder: This work is placed in the public domain, and may be freely used for commercial and non-commercial work with the following conditions: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
WE_WIRL_Rev13.0: Copyright: Würth Elektronik
